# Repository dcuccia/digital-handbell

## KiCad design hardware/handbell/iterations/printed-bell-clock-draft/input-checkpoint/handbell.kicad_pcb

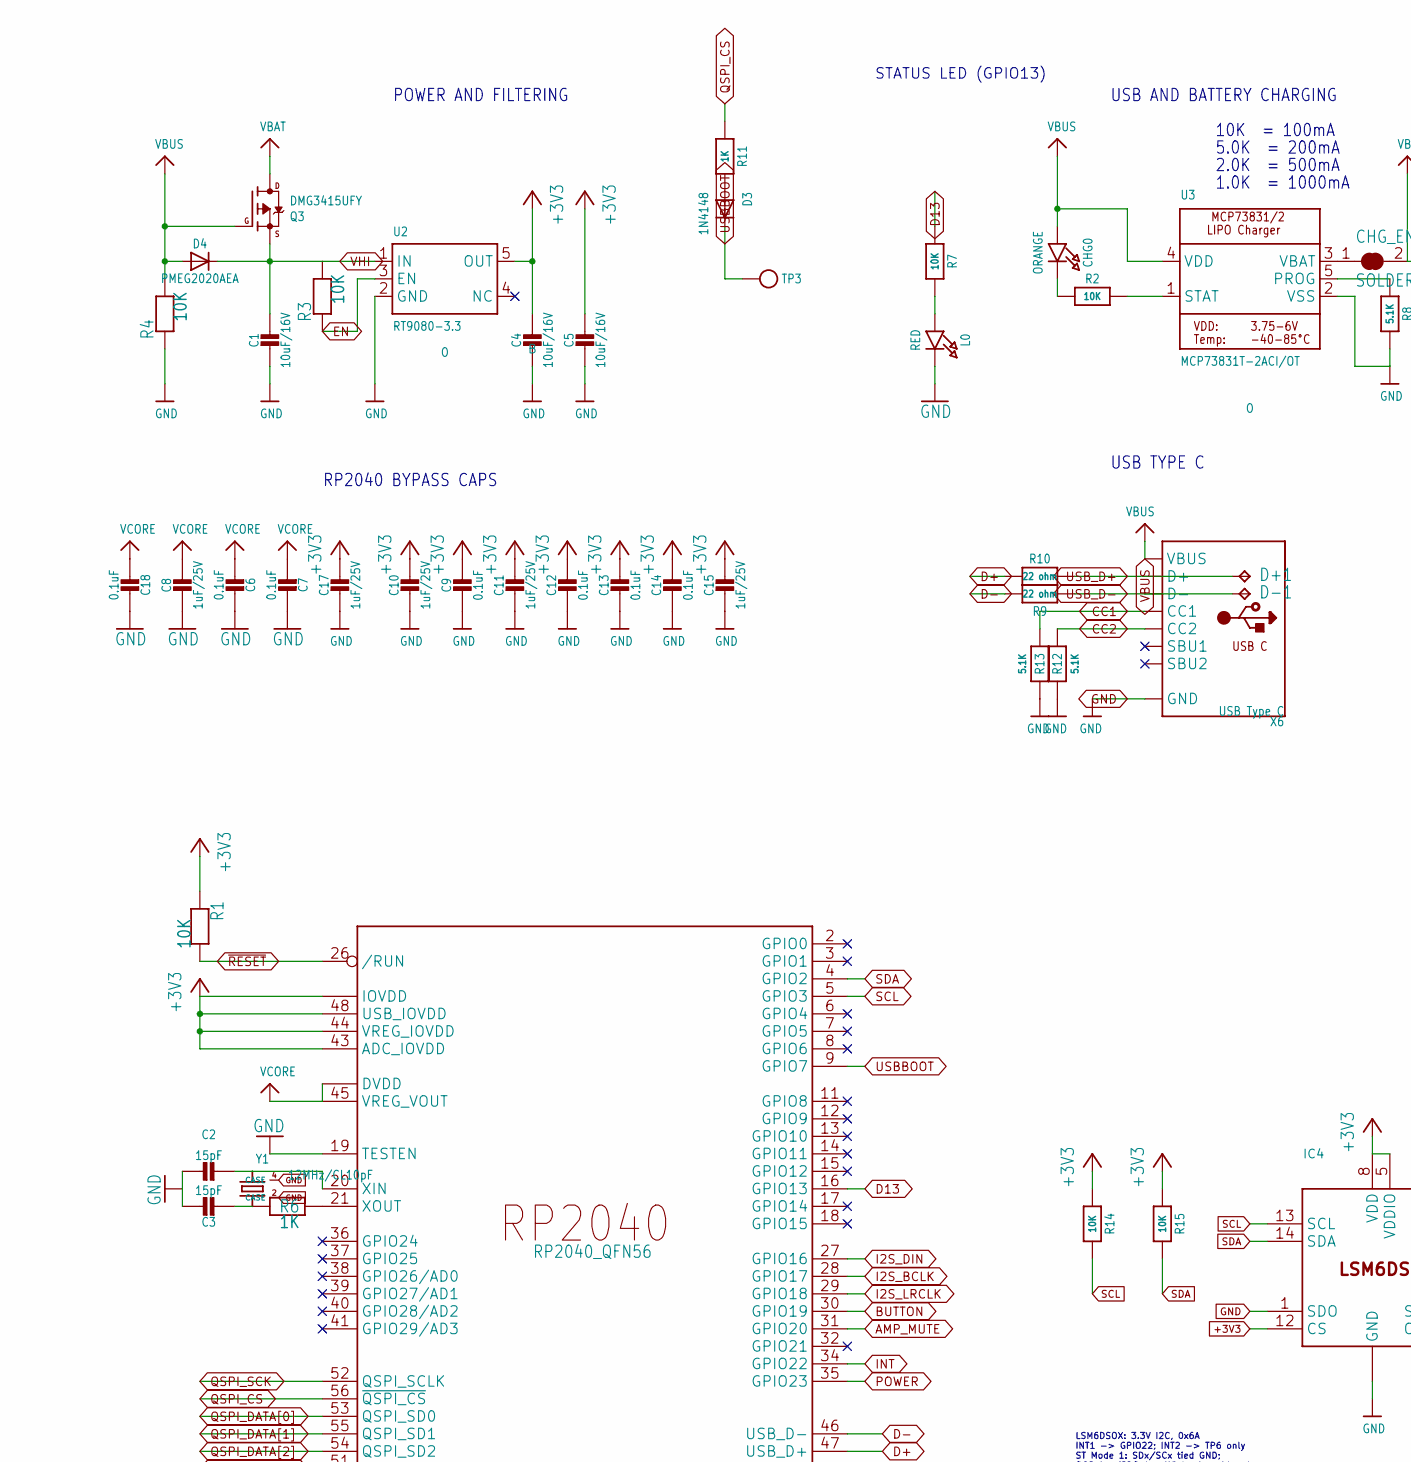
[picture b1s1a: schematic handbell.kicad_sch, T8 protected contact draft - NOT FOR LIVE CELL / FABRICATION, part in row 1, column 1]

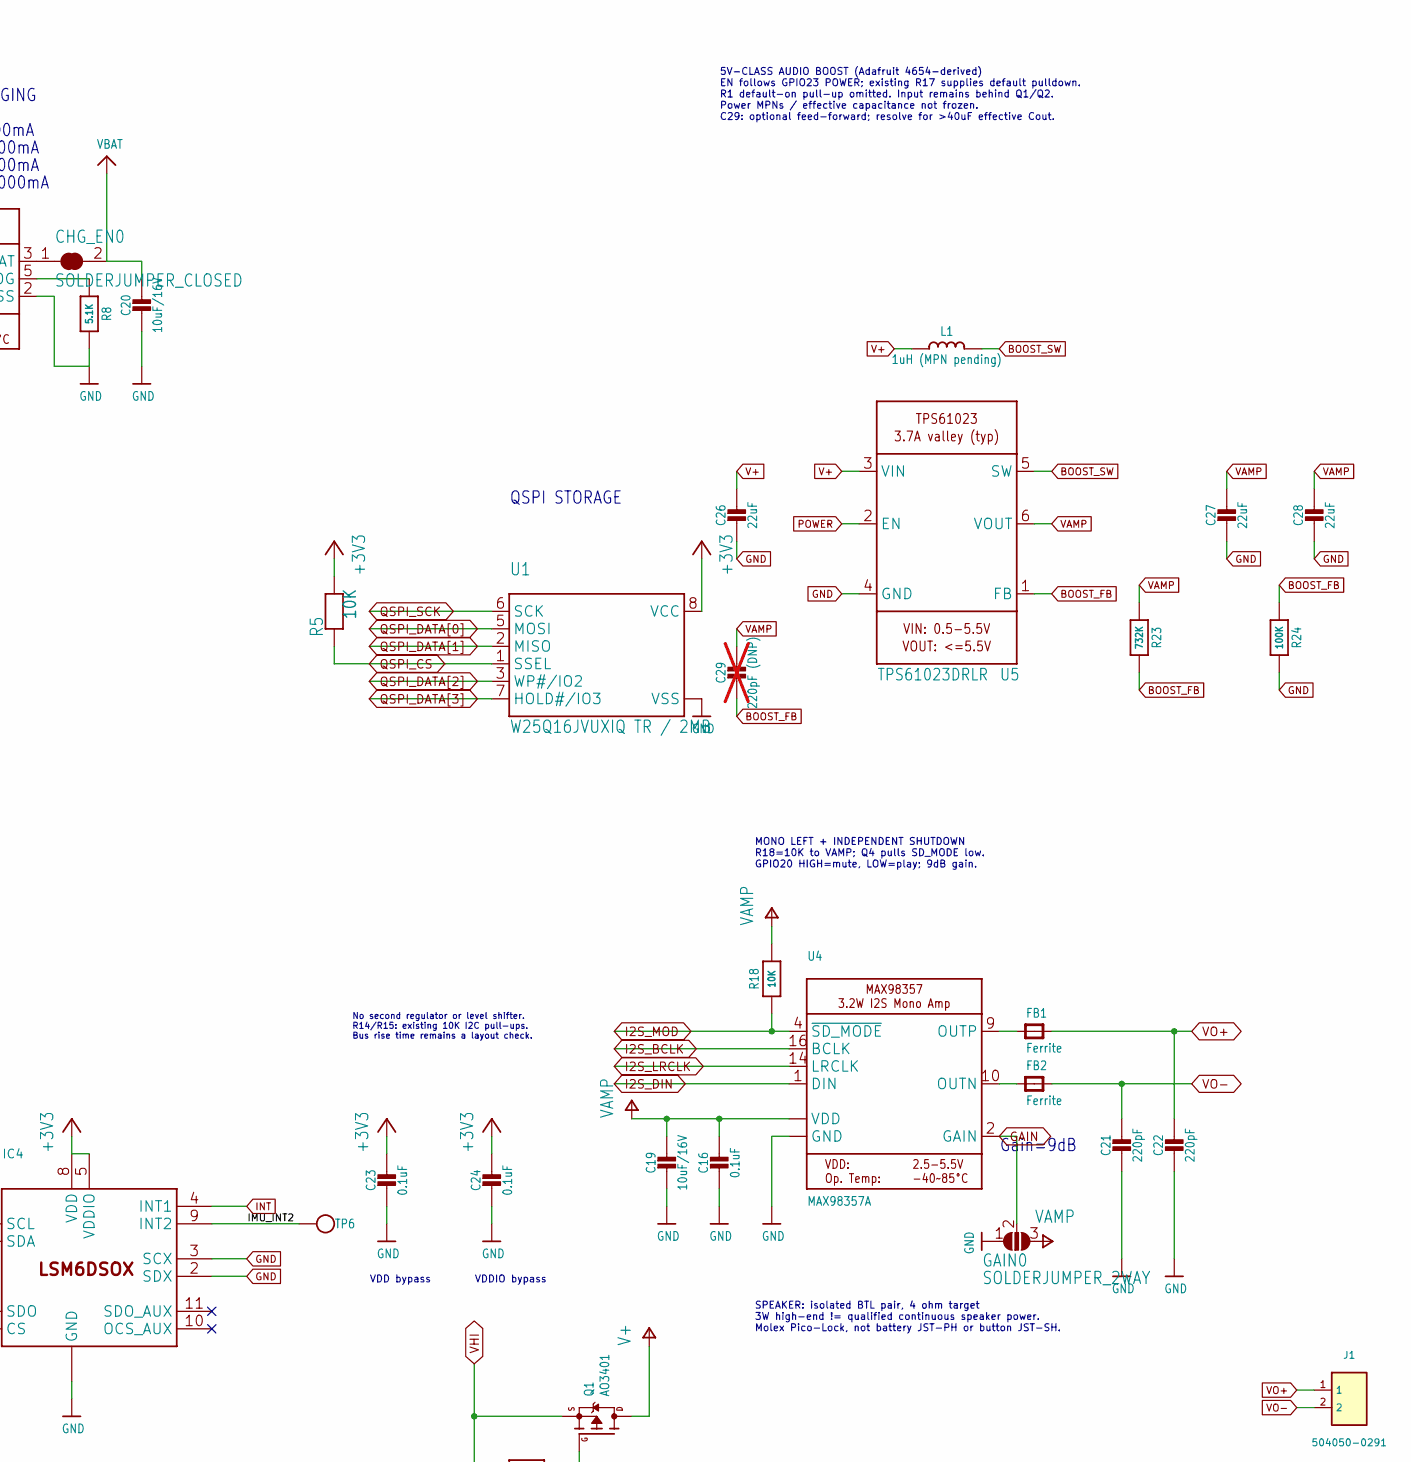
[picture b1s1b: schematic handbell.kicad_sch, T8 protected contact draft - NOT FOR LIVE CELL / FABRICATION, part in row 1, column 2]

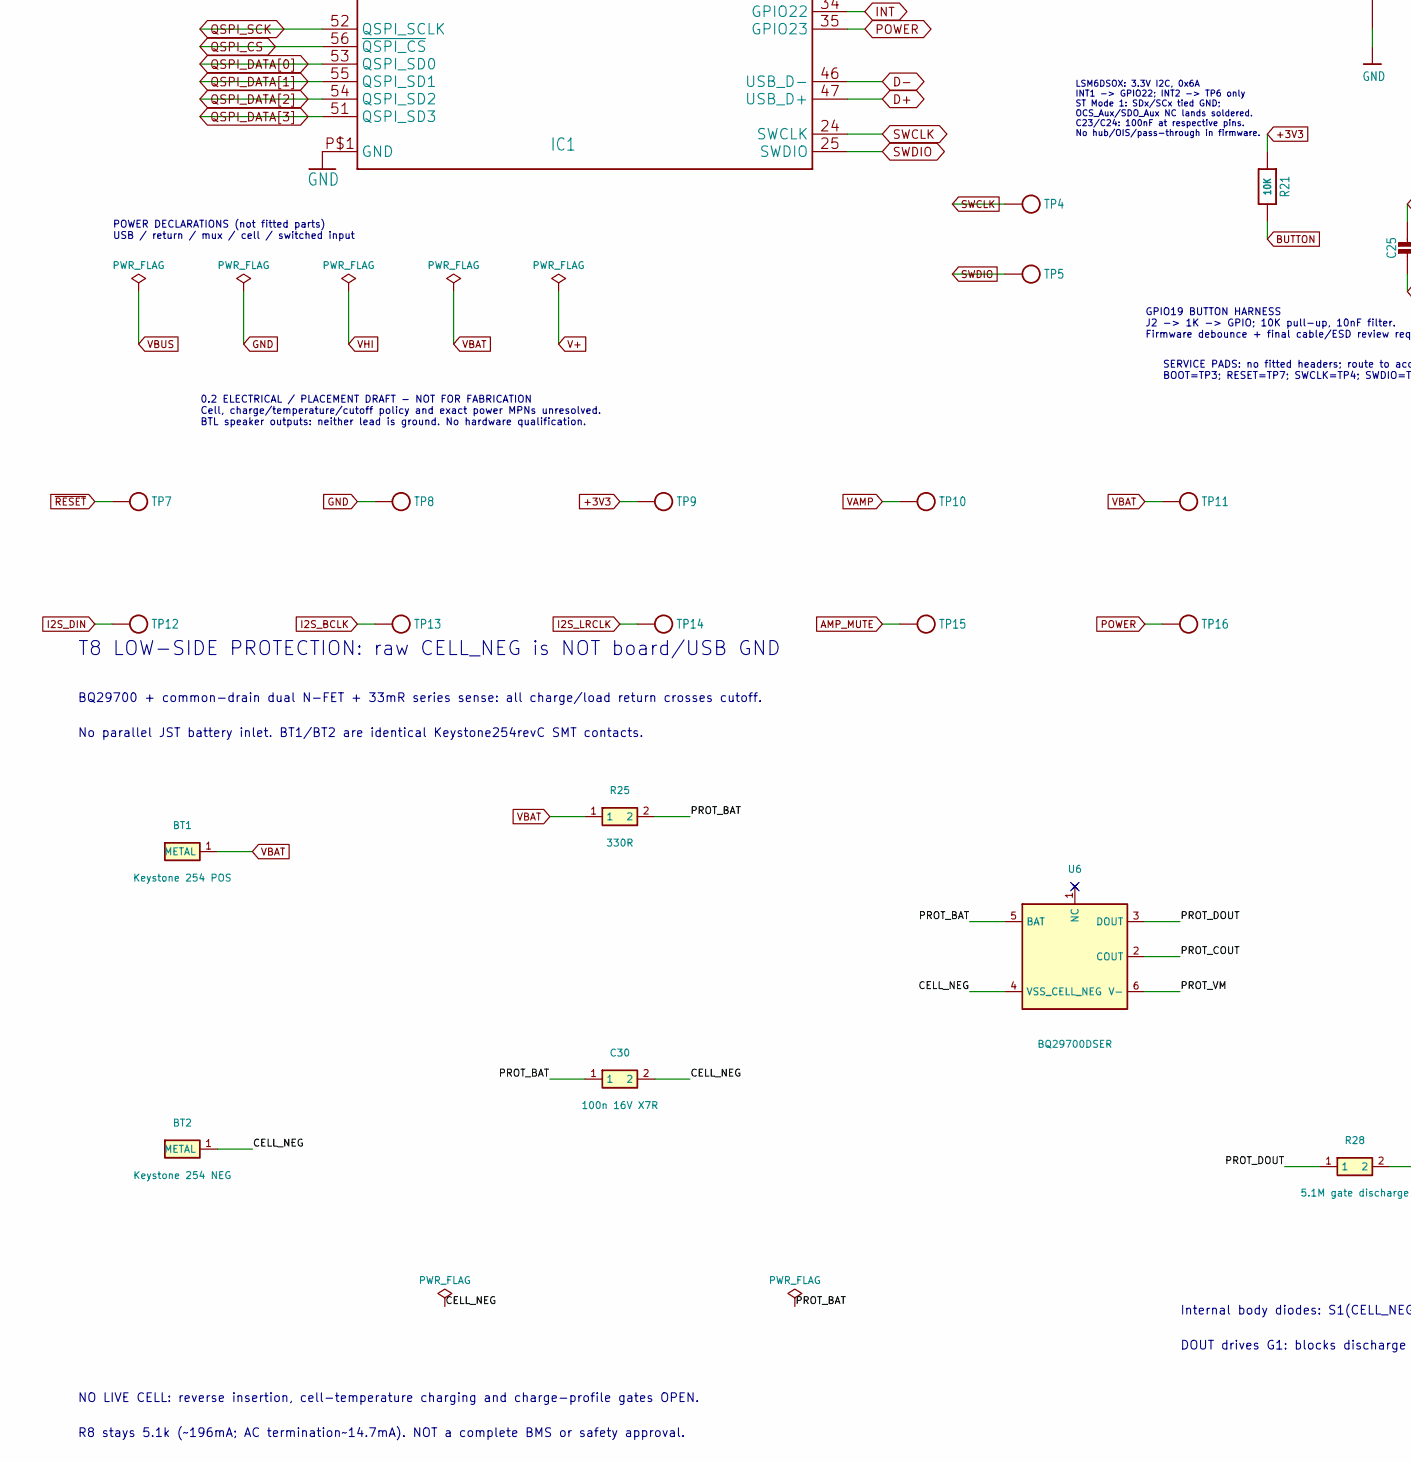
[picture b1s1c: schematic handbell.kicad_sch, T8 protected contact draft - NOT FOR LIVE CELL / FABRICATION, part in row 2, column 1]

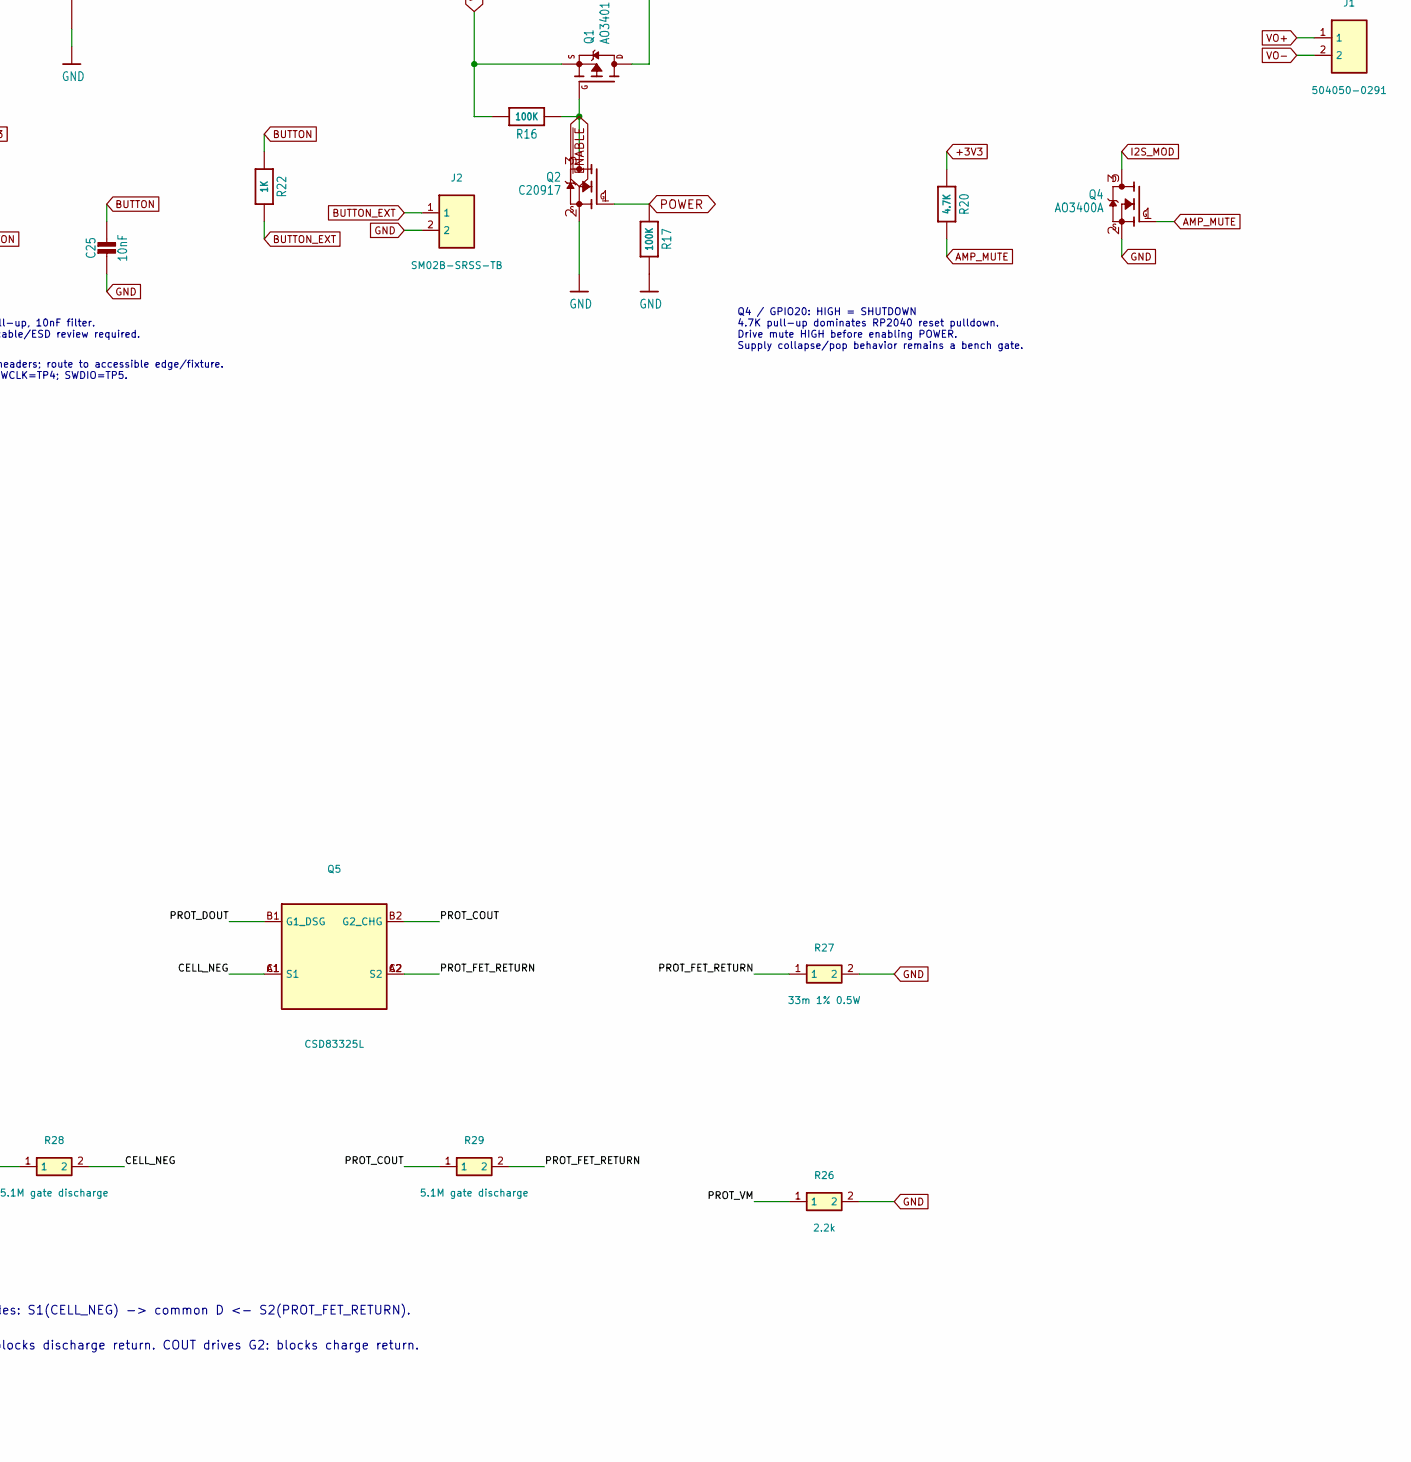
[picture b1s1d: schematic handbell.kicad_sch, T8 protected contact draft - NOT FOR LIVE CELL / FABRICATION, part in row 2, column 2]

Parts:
BT1: Keystone 254 POS; Keystone_254_RevC; MPN 254
BT2: Keystone 254 NEG; Keystone_254_RevC; MPN 254
C1, C4, C5, C19, C20: 10uF/16V; 0805-NO
C2, C3: 15pF; GRM1555C1H150JA01D; MPN GRM1555C1H150JA01D
C6, C7, C9, C12, C13, C14, C16, C18, C23, C24: 0.1uF; _0402NO
C8, C10, C11, C15, C17: 1uF/25V; _0402NO
C21, C22: 220pF; _0402NO
C25: 10nF; _0402NO
C26, C27, C28: 22uF; 0805-NO
C29: 220pF (DNP); _0402NO; not fitted
C30: 100n 16V X7R; _0402NO; MPN GRM155R71C104KA88D
CHG0: ORANGE; CHIPLED_0603_NOOUTLINE
CHG_EN0: SOLDERJUMPER_CLOSED; SolderJumper-2_P1.3mm_Bridged_Pad1.0x1.5mm
D3: 1N4148; SOD-323_MINI
D4: PMEG2020AEA; SOD-323F
D+1: TPB1,27; B1,27
D-1: TPB1,27; B1,27
FB1, FB2: Ferrite; 0603-NO
GAIN0: SOLDERJUMPER_2WAY; SolderJumper-3_P1.3mm_Open_Pad1.0x1.5mm
IC1: RP2040_QFN56; QFN56_7MM_REDUCEDEPAD; LCSC C2040
IC4: LSM6DSOXTR; LGA-14L
J1: 504050-0291; Molex_Pico-Lock_504050-0291_1x02-1MP_P1.50mm_Horizontal; MPN 504050-0291
J2: SM02B-SRSS-TB; JST_SH_SM02B-SRSS-TB_1x02-1MP_P1.00mm_Horizontal; MPN SM02B-SRSS-TB
L0: RED; CHIPLED_0603_NOOUTLINE
L1: 1uH (MPN pending); INDUCTOR_5X5MM_TDK_VLC5045
Q1: AO3401; SOT23-WIDE
Q2: C20917; SOT23-WIDE
Q3: DMG3415UFY; DFN2015-3_DrainPad
Q4: AO3400A; SOT-23; MPN AO3400A
Q5: CSD83325L; CSD83325L_YJE6; MPN CSD83325L
R1, R2, R3, R4, R5, R7, R14, R15, R18, R21: 10K; _0402NO
R6, R11, R22: 1K; _0402NO
R8, R12, R13: 5.1K; _0402NO
R9, R10: 22 ohm; _0402NO
R16, R17, R24: 100K; _0402NO
R20: 4.7K; _0402NO
R23: 732K; _0402NO
R25: 330R; _0402NO; MPN RC0402FR-07330RL
R26: 2.2k; _0402NO; MPN RC0402FR-072K2L
R27: 33m 1% 0.5W; ERJ6BW_0805; MPN ERJ-6BWFR033V
R28, R29: 5.1M gate discharge; _0402NO; MPN RC0402FR-075M1L
TP3, TP4, TP5, TP6: TESTPOINTROUND1.5MMNO; TESTPOINT_ROUND_1.5MM_NO
TP7: ~{RESET}; TESTPOINT_ROUND_1.5MM_NO
TP8: GND; TESTPOINT_ROUND_1.5MM_NO
TP9: +3V3; TESTPOINT_ROUND_1.5MM_NO
TP10: VAMP; TESTPOINT_ROUND_1.5MM_NO
TP11: VBAT; TESTPOINT_ROUND_1.5MM_NO
TP12: I2S_DIN; TESTPOINT_ROUND_1.5MM_NO
TP13: I2S_BCLK; TESTPOINT_ROUND_1.5MM_NO
TP14: I2S_LRCLK; TESTPOINT_ROUND_1.5MM_NO
TP15: AMP_MUTE; TESTPOINT_ROUND_1.5MM_NO
TP16: POWER; TESTPOINT_ROUND_1.5MM_NO
U1: W25Q16JVUXIQ TR / 2MB; Winbond_USON8_UX_2x3; MPN W25Q16JVUXIQ TR
U2: RT9080-3.3; SOT23-5; JLC_ROTATION 0
U3: MCP73831T-2ACI/OT; SOT23-5; JLC_ROTATION 0
U4: MAX98357A; QFN16_3MM
U5: TPS61023DRLR; SOT563; MPN TPS61023DRLR
U6: BQ29700DSER; BQ29700_DSE6; MPN BQ29700DSER
X6: USB Type C; USB_C_CUSB31-CFM2AX-01-X; LCSC C165948
Y1: 12MHz/CL10pF; ABM8_272_T3; MPN ABM8-272-T3

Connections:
+3V3: C4.1, C5.1, C9.1, C10.1, C11.1, C12.1, C13.1, C14.1, C15.1, C17.1, C23.1, C24.1, IC1.1 (IOVDD), IC1.10 (IOVDD), IC1.22 (IOVDD), IC1.33 (IOVDD), IC1.42 (IOVDD), IC1.43 (ADC_IOVDD), IC1.44 (VREG_IOVDD), IC1.48 (USB_IOVDD), IC1.49 (IOVDD), IC4.5 (VDDIO), IC4.8 (VDD), IC4.12 (CS), R1.1, R5.2, R14.1, R15.1, R20.1, R21.1, TP9.P$1 (P$1_P$1), U1.8 (VCC), U2.5 (OUT)
/CELL_NEG: BT2.1 (METAL_1), C30.2, Q5.A1 (S1), Q5.C1 (S1), R28.2, U6.4 (VSS_CELL_NEG)
/IMU_INT2: IC4.9 (INT2), TP6.P$1 (P$1_P$1)
/PROT_BAT: C30.1, R25.2, U6.5 (BAT)
/PROT_COUT: Q5.B2 (G2_CHG), R29.1, U6.2 (COUT)
/PROT_DOUT: Q5.B1 (G1_DSG), R28.1, U6.3 (DOUT)
/PROT_FET_RETURN: Q5.A2 (S2), Q5.C2 (S2), R27.1, R29.2
/PROT_VM: R26.1, U6.6 (V-)
AMP_MUTE: IC1.31 (GPIO20), Q4.1 (G), R20.2, TP15.P$1 (P$1_P$1)
BOOST_FB: C29.2, R23.2, R24.1, U5.1 (FB)
BOOST_SW: L1.P$2 (2), U5.5 (SW)
BUTTON: C25.1, IC1.30 (GPIO19), R21.2, R22.1
BUTTON_EXT: J2.1, R22.2
CC1: R13.2, X6.A5 (CC1)
CC2: R12.2, X6.B5 (CC2)
D13: IC1.16 (GPIO13), R7.1
D+: IC1.47 (USB_D+), R10.2
D-: IC1.46 (USB_D-), R9.2
EN: R3.1, U2.3 (EN)
GAIN: GAIN0.2, U4.2 (GAIN)
GND: C1.2, C2.1, C3.1, C4.2, C5.2, C6.1, C7.1, C8.2, C9.2, C10.2, C11.2, C12.2, C13.2, C14.2, C15.2, C16.2, C17.2, C18.1, C19.2, C20.2, C21.2, C22.2, C23.2, C24.2, C25.2, C26.2, C27.2, C28.2, GAIN0.1, IC1.19 (TESTEN), IC1.P$1 (GND), IC4.1 (SDO), IC4.2 (SDX), IC4.3 (SCX), IC4.6 (GND), IC4.7 (GND), J2.2, L0.C, Q2.2 (S), Q4.2 (S), R4.1, R8.2, R12.1, R13.1, R17.2, R24.2, R26.2, R27.2, TP8.P$1 (P$1_P$1), U1.4 (VSS), U1.PAD (VSS), U2.2 (GND), U3.2 (VSS), U4.3 (GND), U4.11 (GND), U4.15 (GND), U4.THERMAL (GND), U5.4 (GND), X6.A1B12 (GND), X6.B1A12 (GND), Y1.2 (CASE), Y1.4 (CASE); also elsewhere on the board
I2S_BCLK: IC1.28 (GPIO17), TP13.P$1 (P$1_P$1), U4.16 (BCLK)
I2S_DIN: IC1.27 (GPIO16), TP12.P$1 (P$1_P$1), U4.1 (DIN)
I2S_LRCLK: IC1.29 (GPIO18), TP14.P$1 (P$1_P$1), U4.14 (LRCLK)
I2S_MOD: Q4.3 (D), R18.1, U4.4 (~SD_MODE)
INT: IC1.34 (GPIO22), IC4.4 (INT1)
unnamed: C3.2, R6.1, Y1.1
unnamed: CHG0.C, R2.1
unnamed: D3.A, R11.2
unnamed: FB1.1, U4.9 (OUTP)
unnamed: FB2.1, U4.10 (OUTN)
unnamed: C2.2, IC1.20 (XIN), Y1.3 (2)
unnamed: IC1.21 (XOUT), R6.2
unnamed: L0.A, R7.2
unnamed: R8.1, U3.5 (PROG)
unnamed: R2.2, U3.1 (STAT)
unnamed: CHG_EN0.1, U3.3 (VBAT)
POWER: IC1.35 (GPIO23), Q2.1 (G), R17.1, TP16.P$1 (P$1_P$1), U5.2 (EN)
QSPI_CS: IC1.56 (~QSPI_CS), R5.1, R11.1, U1.1 (SSEL)
QSPI_DATA[0]: IC1.53 (QSPI_SD0), U1.5 (MOSI)
QSPI_DATA[1]: IC1.55 (QSPI_SD1), U1.2 (MISO)
QSPI_DATA[2]: IC1.54 (QSPI_SD2), U1.3 (WP#/IO2)
QSPI_DATA[3]: IC1.51 (QSPI_SD3), U1.7 (HOLD#/IO3)
QSPI_SCK: IC1.52 (QSPI_SCLK), U1.6 (SCK)
SCL: IC1.5 (GPIO3), IC4.13 (SCL), R14.2
SDA: IC1.4 (GPIO2), IC4.14 (SDA), R15.2
SWCLK: IC1.24 (SWCLK), TP4.P$1 (P$1_P$1)
SWDIO: IC1.25 (SWDIO), TP5.P$1 (P$1_P$1)
USBBOOT: D3.C, IC1.9 (GPIO7), TP3.P$1 (P$1_P$1)
USB_D+: D+1.TP (TP_TP), R10.1, X6.A6 (D+), X6.B6 (D+)
USB_D-: D-1.TP (TP_TP), R9.1, X6.A7 (D-), X6.B7 (D-)
V+: C26.1, L1.P$1 (1), Q1.3 (D), U5.3 (VIN)
VAMP: C16.1, C19.1, C27.1, C28.1, C29.1, GAIN0.3, R18.2, R23.1, TP10.P$1 (P$1_P$1), U4.7 (VDD), U4.8 (VDD), U5.6 (VOUT)
VBAT: BT1.1 (METAL_1), C20.1, CHG_EN0.2, Q3.3 (D), R25.1, TP11.P$1 (P$1_P$1)
VBUS: CHG0.A, D4.A, Q3.1 (G), R4.2, U3.4 (VDD), X6.A4B9 (VBUS), X6.B4A9 (VBUS)
VCORE: C6.2, C7.2, C8.1, C18.2, IC1.23 (DVDD), IC1.45 (VREG_VOUT), IC1.50 (DVDD)
VHI: C1.1, D4.C, Q1.2 (S), Q3.2 (S), R3.2, R16.2, U2.1 (IN)
VO+: C22.1, FB1.2, J1.1
VO-: C21.1, FB2.2, J1.2
~ENABLE: Q1.1 (G), Q2.3 (D), R16.1
~RESET: IC1.26 (/RUN), R1.2, TP7.P$1 (P$1_P$1)

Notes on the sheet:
POWER AND FILTERING
MONO LEFT + INDEPENDENT SHUTDOWN R18=10K to VAMP; Q4 pulls SD_MODE low. GPIO20 HIGH=mute, LOW=play; 9dB gain.
USB AND BATTERY CHARGING
Gain=9dB
STATUS LED (GPIO13)
QSPI STORAGE
USB TYPE C
RP2040 BYPASS CAPS
5.0K = 200mA
2.0K = 500mA
10K = 100mA
1.0K = 1000mA
POWER DECLARATIONS (not fitted parts) USB / return / mux / cell / switched input
0.2 ELECTRICAL / PLACEMENT DRAFT - NOT FOR FABRICATION Cell, charge/temperature/cutoff policy and exact power MPNs unresolved. BTL speaker outputs: neither lead is ground. No hardware qualification.
VDD bypass
VDDIO bypass
LSM6DSOX: 3.3V I2C, 0x6A INT1 -> GPIO22; INT2 -> TP6 only ST Mode 1: SDx/SCx tied GND; OCS_Aux/SDO_Aux NC lands soldered. C23/C24: 100nF at respective pins. No hub/OIS/pass-through in firmware.
No second regulator or level shifter. R14/R15: existing 10K I2C pull-ups. Bus rise time remains a layout check.
5V-CLASS AUDIO BOOST (Adafruit 4654-derived) EN follows GPIO23 POWER; existing R17 supplies default pulldown. R1 default-on pull-up omitted. Input remains behind Q1/Q2. Power MPNs / effective capacitance not frozen. C29: optional feed-forward; resolve for >40uF effective Cout.
GPIO19 BUTTON HARNESS J2 -> 1K -> GPIO; 10K pull-up, 10nF filter. Firmware debounce + final cable/ESD review required.
Q4 / GPIO20: HIGH = SHUTDOWN 4.7K pull-up dominates RP2040 reset pulldown. Drive mute HIGH before enabling POWER. Supply collapse/pop behavior remains a bench gate.
SPEAKER: isolated BTL pair, 4 ohm target 3W high-end != qualified continuous speaker power. Molex Pico-Lock, not battery JST-PH or button JST-SH.
SERVICE PADS: no fitted headers; route to accessible edge/fixture. BOOT=TP3; RESET=TP7; SWCLK=TP4; SWDIO=TP5.
T8 LOW-SIDE PROTECTION: raw CELL_NEG is NOT board/USB GND
BQ29700 + common-drain dual N-FET + 33mR series sense: all charge/load return crosses cutoff.
No parallel JST battery inlet. BT1/BT2 are identical Keystone254revC SMT contacts.
Internal body diodes: S1(CELL_NEG) -> common D <- S2(PROT_FET_RETURN).
DOUT drives G1: blocks discharge return. COUT drives G2: blocks charge return.
NO LIVE CELL: reverse insertion, cell-temperature charging and charge-profile gates OPEN.
R8 stays 5.1k (~196mA; AC termination~14.7mA). NOT a complete BMS or safety approval.

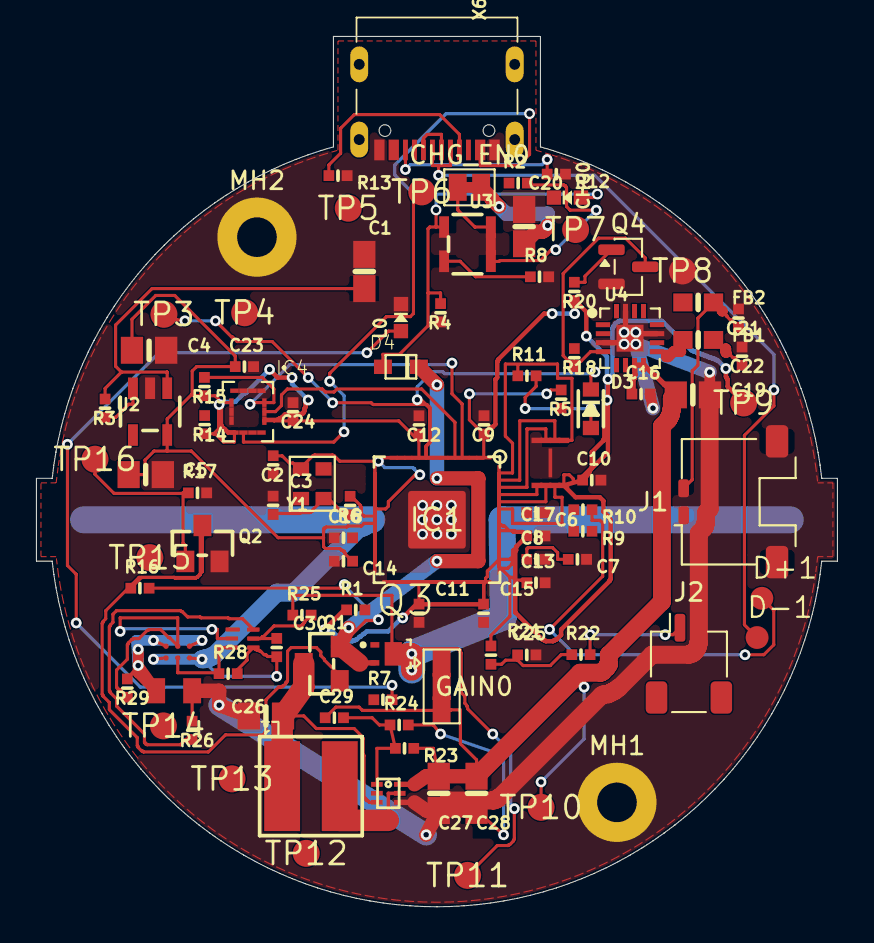
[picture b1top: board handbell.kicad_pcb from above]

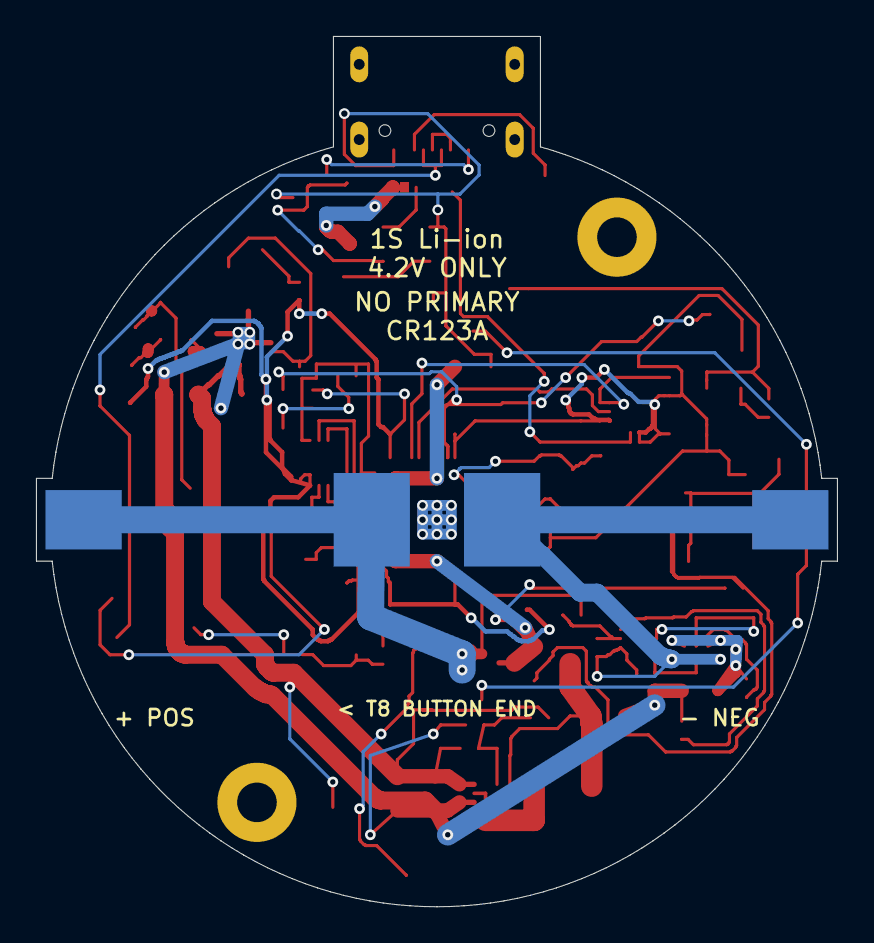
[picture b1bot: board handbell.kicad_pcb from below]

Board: 2 copper layers, 44.5 x 48.3 mm, 104 parts (2 on the bottom side), 61 nets.

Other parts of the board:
MH1, MH2: M2 GND mounting hole; MountingHole_2.2mm_M2_Pad

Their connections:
GND: MH1.1, MH2.1; also elsewhere on the board

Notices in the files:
hardware/handbell/iterations/printed-bell-clock-draft/handbell.kicad_sch:
Adapted from Adafruit 5768 / 4438 / 4654; CC BY-SA 3.0. See ATTRIBUTION.md.
